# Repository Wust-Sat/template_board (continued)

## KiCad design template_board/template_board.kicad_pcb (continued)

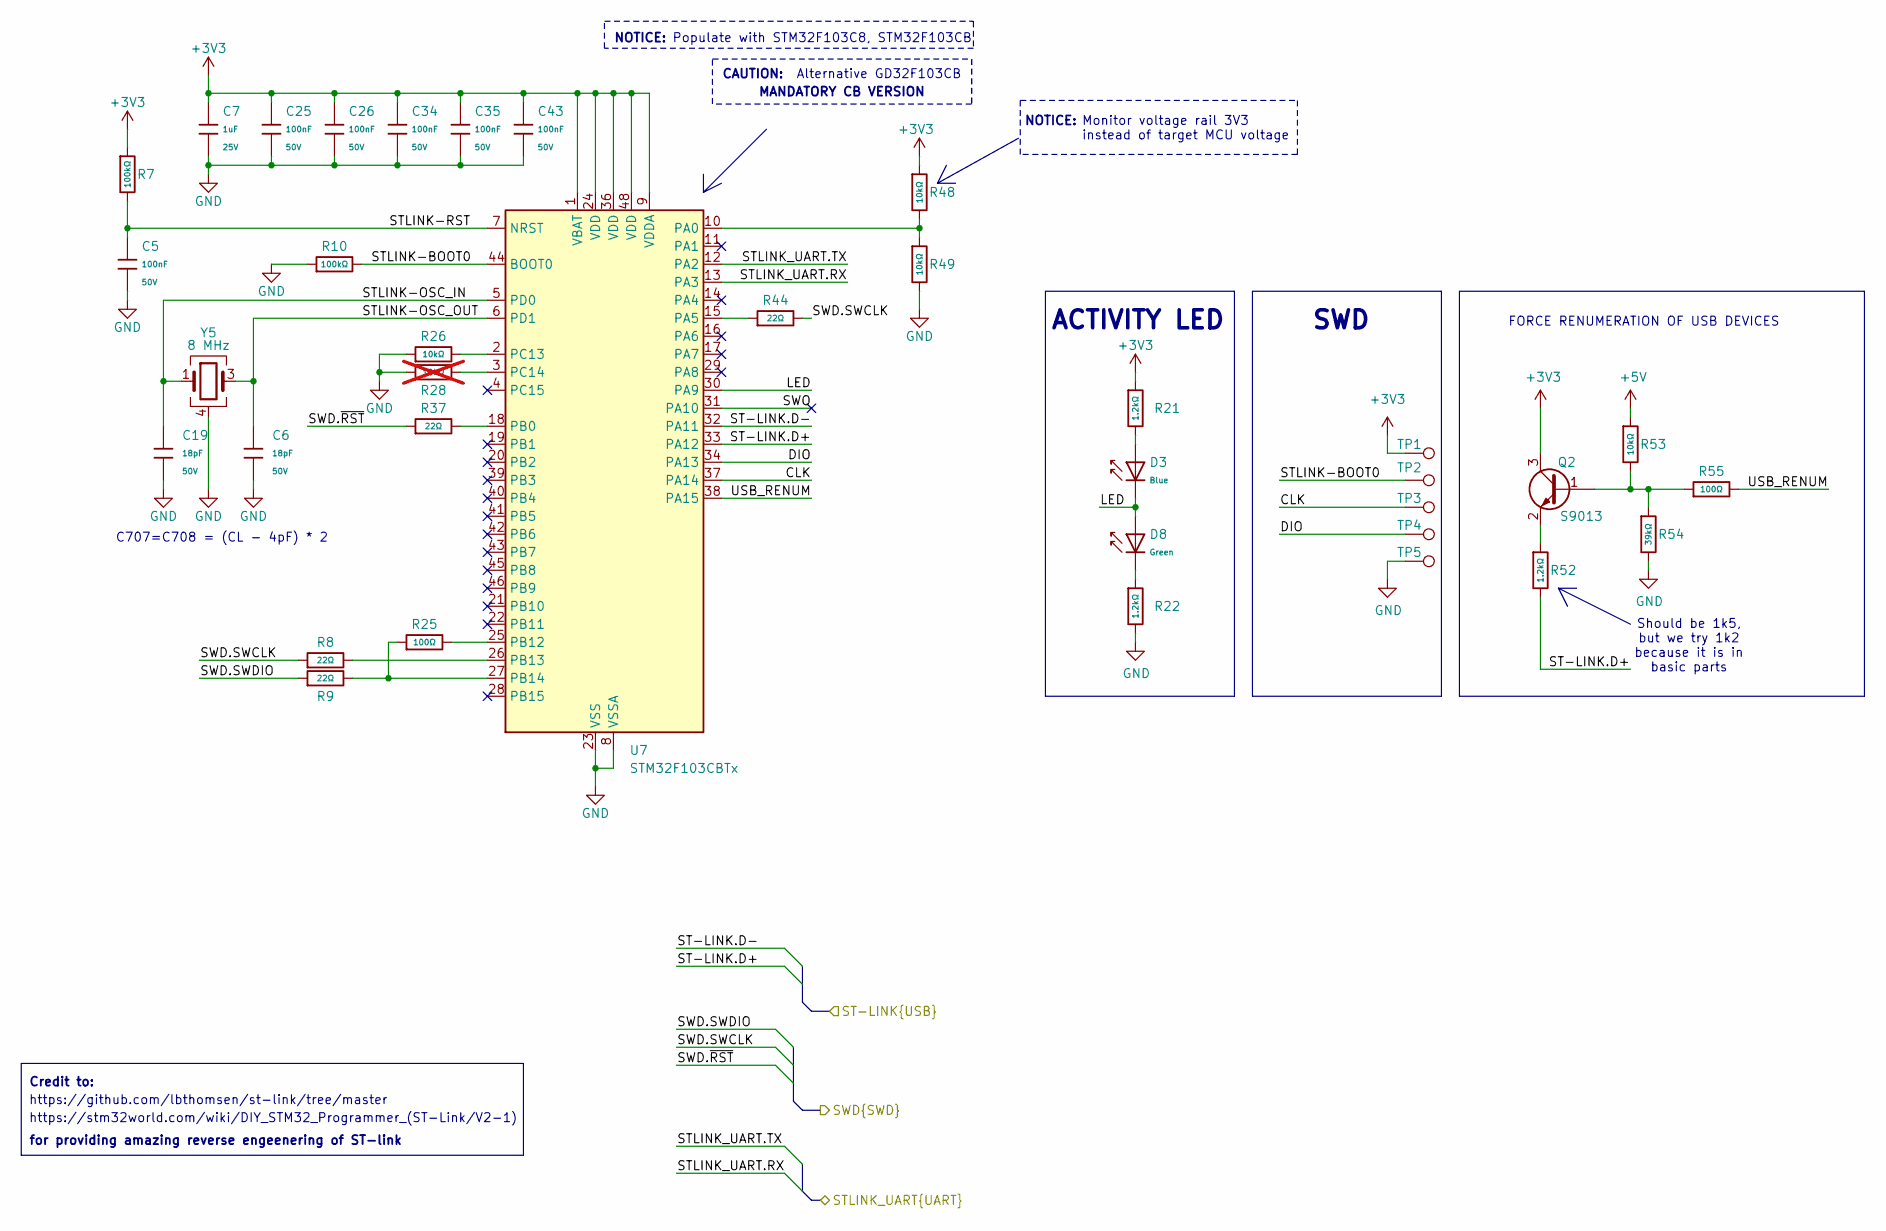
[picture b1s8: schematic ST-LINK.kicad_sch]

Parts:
C5, C25, C26, C34, C35, C43: 100nF; C_0402; Voltage Rated 50V; Tolerance ±10%; Part CL05B104KB54PNC; LCSC C307331
C6, C19: 18pF; C_0402; Voltage Rated 50V; Tolerance ±5%; Part 0402CG180J500NT; LCSC C1549
C7: 1uF; C_0402; Voltage Rated 25V; Tolerance ±10%; Part CL05A105KA5NQNC; LCSC C52923
D3: Blue; D_0603; Part 19-217/BHC-ZL1M2RY/6T; LCSC C2986058
D8: Green; D_0603; Part 19-217/GHC-YR1S2/6T; LCSC C2986059
Q2: S9013; SOT-23; LCSC C6749
R7, R10: 100kΩ; R_0402; Overload Voltage (Max) 50V; Tolerance ±1%; Part 0402WGF1003TCE; LCSC C25741
R8, R9, R37, R44: 22Ω; R_0402; Overload Voltage (Max) 50V; Tolerance ±1%; Part 0402WGF220JTCE; LCSC C25092
R21, R22, R52: 1.2kΩ; R_0402; Overload Voltage (Max) 50V; Tolerance ±1%; Part 0402WGF1201TCE; LCSC C25862
R25, R55: 100Ω; R_0402; Overload Voltage (Max) 50V; Tolerance ±1%; Part 0402WGF1000TCE; LCSC C25076
R26, R48, R49, R53: 10kΩ; R_0402; Overload Voltage (Max) 50V; Tolerance ±1%; Part 0402WGF1002TCE; LCSC C25744
R28: 10kΩ; R_0402; Overload Voltage (Max) 50V; Tolerance ±1%; Part 0402WGF1002TCE; LCSC C25744; not fitted
R54: 39kΩ; R_0402; Overload Voltage (Max) 50V; Tolerance ±1%; Part 0402WGF3902TCE; LCSC C25783
TP1, TP2, TP3, TP4, TP5: TestPoint_Pad_D1.0mm
U7: STM32F103CBTx; LQFP-48_7x7mm_P0.5mm
Y5: 8 MHz; CRYSTAL-SMD_4P-L3.2-W2.5-BL

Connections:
+3V3: C7.1, C25.1, C26.1, C34.1, C35.1, C43.1, Q2.3 (C), R7.1, R21.1, R48.1, TP1.1, U7.1 (VBAT), U7.9 (VDDA), U7.24 (VDD), U7.36 (VDD), U7.48 (VDD); also elsewhere on the board
+5V: R53.1; also elsewhere on the board
/MCU/STLINK_UART.RX: U7.13 (PA3); also elsewhere on the board
/MCU/STLINK_UART.TX: U7.12 (PA2); also elsewhere on the board
/MCU/SWD.SWCLK: R8.1, R44.2; also elsewhere on the board
/MCU/SWD.SWDIO: R9.1; also elsewhere on the board
/MCU/SWD.~RST: R37.1; also elsewhere on the board
/ST-LINK/CLK: TP3.1, U7.37 (PA14)
/ST-LINK/DIO: TP4.1, U7.34 (PA13)
/ST-LINK/LED: D3.1, D8.2, U7.30 (PA9)
/ST-LINK/ST-LINK.D+: R52.2, U7.33 (PA12); also elsewhere on the board
/ST-LINK/ST-LINK.D-: U7.32 (PA11); also elsewhere on the board
/ST-LINK/STLINK-BOOT0: R10.2, TP2.1, U7.44 (BOOT0)
/ST-LINK/STLINK-OSC_IN: C19.1, U7.5 (PD0), Y5.1
/ST-LINK/STLINK-OSC_OUT: C6.1, U7.6 (PD1), Y5.3
/ST-LINK/STLINK-RST: C5.1, R7.2, U7.7 (NRST)
/ST-LINK/SWO: U7.31 (PA10)
/ST-LINK/USB_RENUM: R55.2, U7.38 (PA15)
GND: C5.2, C6.2, C7.2, C19.2, C25.2, C26.2, C34.2, C35.2, C43.2, R10.1, R22.2, R26.1, R28.1, R49.2, R54.2, TP5.1, U7.8 (VSSA), U7.23 (VSS), U7.35 (VSS), U7.47 (VSS), Y5.2, Y5.4; also elsewhere on the board
unnamed: D3.2, R21.2
unnamed: D8.1, R22.1
unnamed: Q2.1 (B), R53.2, R54.1, R55.1
unnamed: Q2.2 (E), R52.1
unnamed: R48.2, R49.1, U7.10 (PA0)
unnamed: R44.1, U7.15 (PA5)
unnamed: R37.2, U7.18 (PB0)
unnamed: R25.2, U7.25 (PB12)
unnamed: R8.2, U7.26 (PB13)
unnamed: R9.2, R25.1, U7.27 (PB14)
unnamed: R26.2, U7.2 (PC13)
unnamed: R28.2, U7.3 (PC14)

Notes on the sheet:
FORCE RENUMERATION OF USB DEVICES
ACTIVITY LED
MANDATORY CB VERSION
CAUTION:
Should be 1k5, but we try 1k2 because it is in basic parts
SWD
Monitor voltage rail 3V3 instead of target MCU voltage
for providing amazing reverse engeenering of ST-link
NOTICE:
https://stm32world.com/wiki/DIY_STM32_Programmer_(ST-Link/V2-1)
https://github.com/lbthomsen/st-link/tree/master
Credit to:
C707=C708 = (CL - 4pF) * 2
Alternative GD32F103CB
Populate with STM32F103C8, STM32F103CB

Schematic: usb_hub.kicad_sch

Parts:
C47: 100nF; C_0402; Voltage Rated 50V; Tolerance ±10%; Part CL05B104KB54PNC; LCSC C307331
C48: 10uF; C_0402; Voltage Rated 6.3V; Tolerance ±20%; Part CL05A106MQ5NUNC; LCSC C15525
C49: 1uF; C_0402; Voltage Rated 25V; Tolerance ±10%; Part CL05A105KA5NQNC; LCSC C52923
D9: Red; D_0603; Part KT-0603R; LCSC C2286
R64, R65, R66, R67: 22Ω; R_0402; Overload Voltage (Max) 50V; Tolerance ±1%; Part 0402WGF220JTCE; LCSC C25092
R68: 1kΩ; R_0402; Overload Voltage (Max) 50V; Tolerance ±1%; Part 0402WGF1001TCE; LCSC C11702
U12: CH334P; QFN-16-1EP_3x3mm_P0.5mm_EP1.7x1.7mm
Y6: 12Mhz; Crystal_SMD_3225-4Pin_3.2x2.5mm

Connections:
+5V: C49.1, D9.2, U12.15 (5V); also elsewhere on the board
/MCU/USB_MCU.D+: R65.1; also elsewhere on the board
/MCU/USB_MCU.D-: R64.1; also elsewhere on the board
/ST-LINK/ST-LINK.D+: R67.1; also elsewhere on the board
/ST-LINK/ST-LINK.D-: R66.1; also elsewhere on the board
/USB-C/EXTUSB.D+: U12.12 (DPU); also elsewhere on the board
/USB-C/EXTUSB.D-: U12.11 (DMU); also elsewhere on the board
/USB_HUB/USBOUT1_R.D+: R67.2, U12.4 (DP4)
/USB_HUB/USBOUT1_R.D-: R66.2, U12.3 (DM4)
/USB_HUB/USB_MCU_R.D+: R65.2, U12.6 (DP3)
/USB_HUB/USB_MCU_R.D-: R64.2, U12.5 (DM3)
GND: C47.2, C48.2, C49.2, U12.17 (GND), Y6.2, Y6.4; also elsewhere on the board
unnamed: D9.1, R68.2
unnamed: C47.1, C48.1, U12.16 (3V3)
unnamed: R68.1, U12.14 (PGANG)
unnamed: U12.2 (XI), Y6.3
unnamed: U12.1 (XO), Y6.1

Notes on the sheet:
USB HUB TO MCU AND STLINK

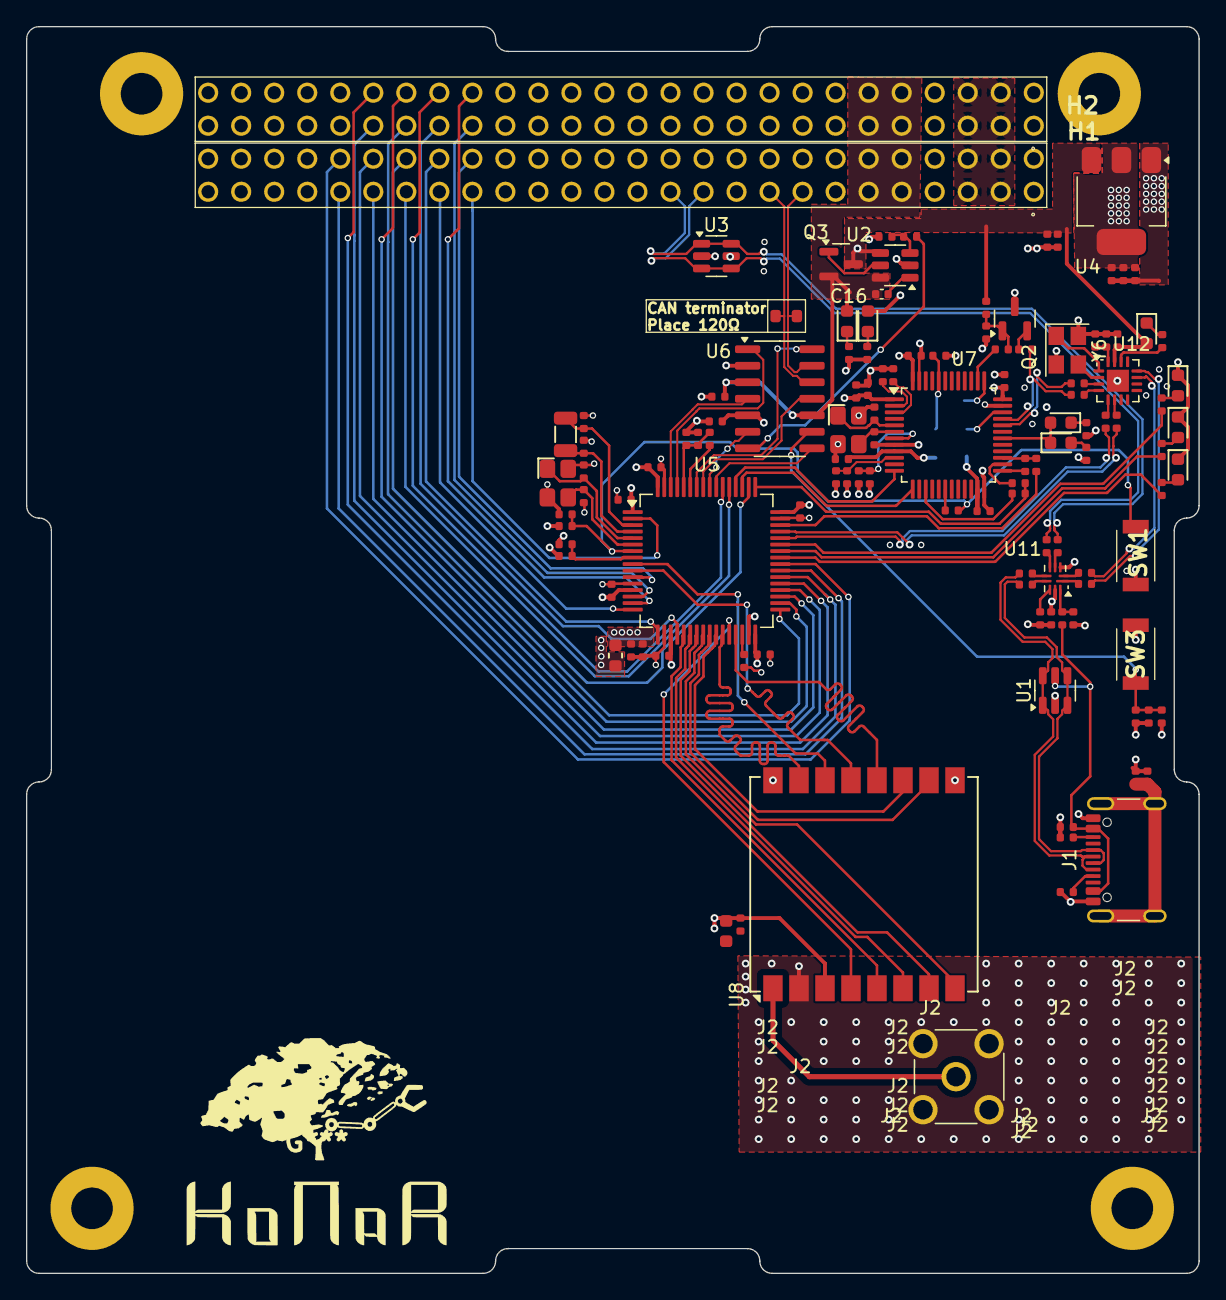
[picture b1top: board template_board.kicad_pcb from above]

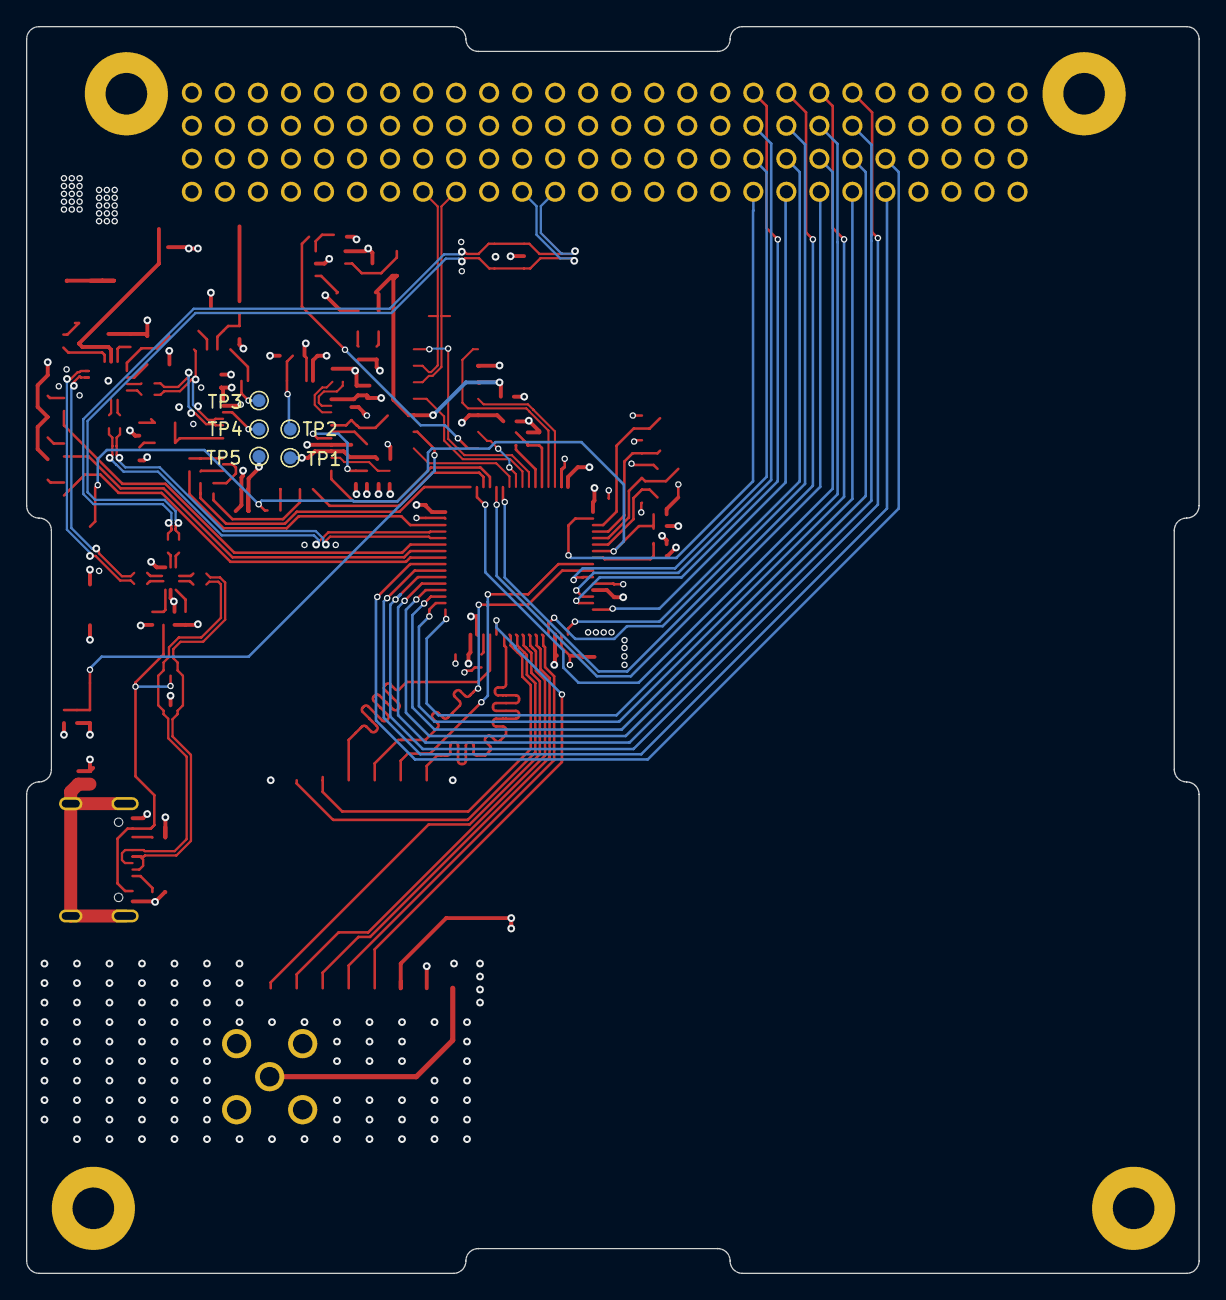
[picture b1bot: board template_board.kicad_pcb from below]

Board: 4 copper layers, 90.2 x 95.9 mm, 128 parts (5 on the bottom side), 121 nets.

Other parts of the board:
M1, M3: MountingHole; MountingHole_3.2mm_M3_Pad

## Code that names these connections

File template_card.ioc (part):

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Mcu.Name=STM32U575RITx
Mcu.Package=LQFP64
Mcu.UserName=STM32U575RITx
PA10.Signal=GPIO_Output
PA11.Mode=Device_Only
PA11.Signal=USB_OTG_FS_DM
PA12.Mode=Device_Only
PA12.Signal=USB_OTG_FS_DP
PA13\ (JTMS/SWDIO).Mode=Serial_Wire
PA13\ (JTMS/SWDIO).Signal=DEBUG_JTMS-SWDIO
PA14\ (JTCK/SWCLK).Mode=Serial_Wire
PA14\ (JTCK/SWCLK).Signal=DEBUG_JTCK-SWCLK
PA8.Signal=GPIO_Output
PA9.Signal=GPIO_Output
PB3\ (JTDO/TRACESWO).Mode=Full_Duplex_Master
PB3\ (JTDO/TRACESWO).Signal=SPI1_SCK
PB4\ (NJTRST).Mode=Full_Duplex_Master
PB4\ (NJTRST).Signal=SPI1_MISO
PB5.Mode=Full_Duplex_Master
PB5.Signal=SPI1_MOSI
PB6.Signal=GPIO_Output
PB7.Signal=GPIO_Output
PB8.Mode=FDCAN_Activate
PB8.Signal=FDCAN1_RX
PB9.Mode=FDCAN_Activate
PB9.Signal=FDCAN1_TX
PC0.Mode=IN1-Single-Ended
PC0.Signal=ADC1_IN1
PC10.Mode=Asynchronous
PC10.Signal=UART4_TX
PC11.Mode=Asynchronous
PC11.Signal=UART4_RX
PC14-OSC32_IN\ (PC14).Mode=LSE-External-Oscillator
PC14-OSC32_IN\ (PC14).Signal=RCC_OSC32_IN
PC15-OSC32_OUT\ (PC15).Mode=LSE-External-Oscillator
PC15-OSC32_OUT\ (PC15).Signal=RCC_OSC32_OUT
PH0-OSC_IN\ (PH0).Mode=HSE-External-Oscillator
PH0-OSC_IN\ (PH0).Signal=RCC_OSC_IN
PH1-OSC_OUT\ (PH1).Mode=HSE-External-Oscillator
PH1-OSC_OUT\ (PH1).Signal=RCC_OSC_OUT
RCC.HSE_VALUE=12000000
RCC.SYSCLKFreq_VALUE=160000000
RCC.SYSCLKSource=RCC_SYSCLKSOURCE_PLLCLK
board=custom

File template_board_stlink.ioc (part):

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Mcu.Name=STM32F303C(B-C)Tx
Mcu.Package=LQFP48
Mcu.UserName=STM32F303CBTx
PA0.Mode=IN1-Single-Ended
PA0.Signal=ADC1_IN1
PA11.Mode=Device
PA11.Signal=USB_DM
PA12.Mode=Device
PA12.Signal=USB_DP
PA13.Mode=Serial_Wire
PA13.Signal=SYS_JTMS-SWDIO
PA14.Mode=Serial_Wire
PA14.Signal=SYS_JTCK-SWCLK
PB3.Signal=GPIO_Output
PB4.Signal=GPIO_Output
PB5.Signal=GPIO_Output
PB6.Mode=I2C
PB6.Signal=I2C1_SCL
PB7.Mode=I2C
PB7.Signal=I2C1_SDA
PB8.Mode=CAN_Activate
PB8.Signal=CAN_RX
PB9.Mode=CAN_Activate
PB9.Signal=CAN_TX
PC13.Signal=GPIO_Output
PC14-OSC32_IN.Signal=GPIO_Output
PC15-OSC32_OUT.Signal=GPIO_Input
PF0-OSC_IN.Mode=HSE-External-Oscillator
PF0-OSC_IN.Signal=RCC_OSC_IN
PF1-OSC_OUT.Mode=HSE-External-Oscillator
PF1-OSC_OUT.Signal=RCC_OSC_OUT
RCC.HSEPLLFreq_Value=8000000
RCC.HSE_VALUE=8000000
RCC.SYSCLKFreq_VALUE=72000000
RCC.SYSCLKSourceVirtual=RCC_SYSCLKSOURCE_PLLCLK
board=custom

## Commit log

2025-03-13 init repo
2025-03-14 added newm mcu on a side
2025-03-15 u5 wip
2025-03-15 updated all subschematics
2025-03-15 update ioc file for the mcu
2025-03-15 update pcb leyout goruping
2025-03-16 added can fb transiver
2025-03-16 rysuneczek
2025-03-16 can transiver update
2025-03-17 chamt skończony chyba
2025-03-17 schemat skończony
2025-03-17 stated leyout
2025-03-17 sub leyoyut partially completed
2025-03-19 migtade ioc to mx version 6.14
2025-03-20 layout 95% completed
2025-03-20 drc fixed
2025-03-28 [schematics] fixed issue with: stlink->crystal capacitors, usb-> esd with too big capacitance, tranzistor for stlink-usb renum changed
2025-03-28 [schematics] changed stlink SWD pins
2025-04-15 [schematics] complete lora board
2025-04-16 fixed USB\Power leyout , added proper RF rules adn paths
2025-04-23 fixed SPI leyoud, added length matching
2025-04-23 pubmed up kicad version to 9.0
